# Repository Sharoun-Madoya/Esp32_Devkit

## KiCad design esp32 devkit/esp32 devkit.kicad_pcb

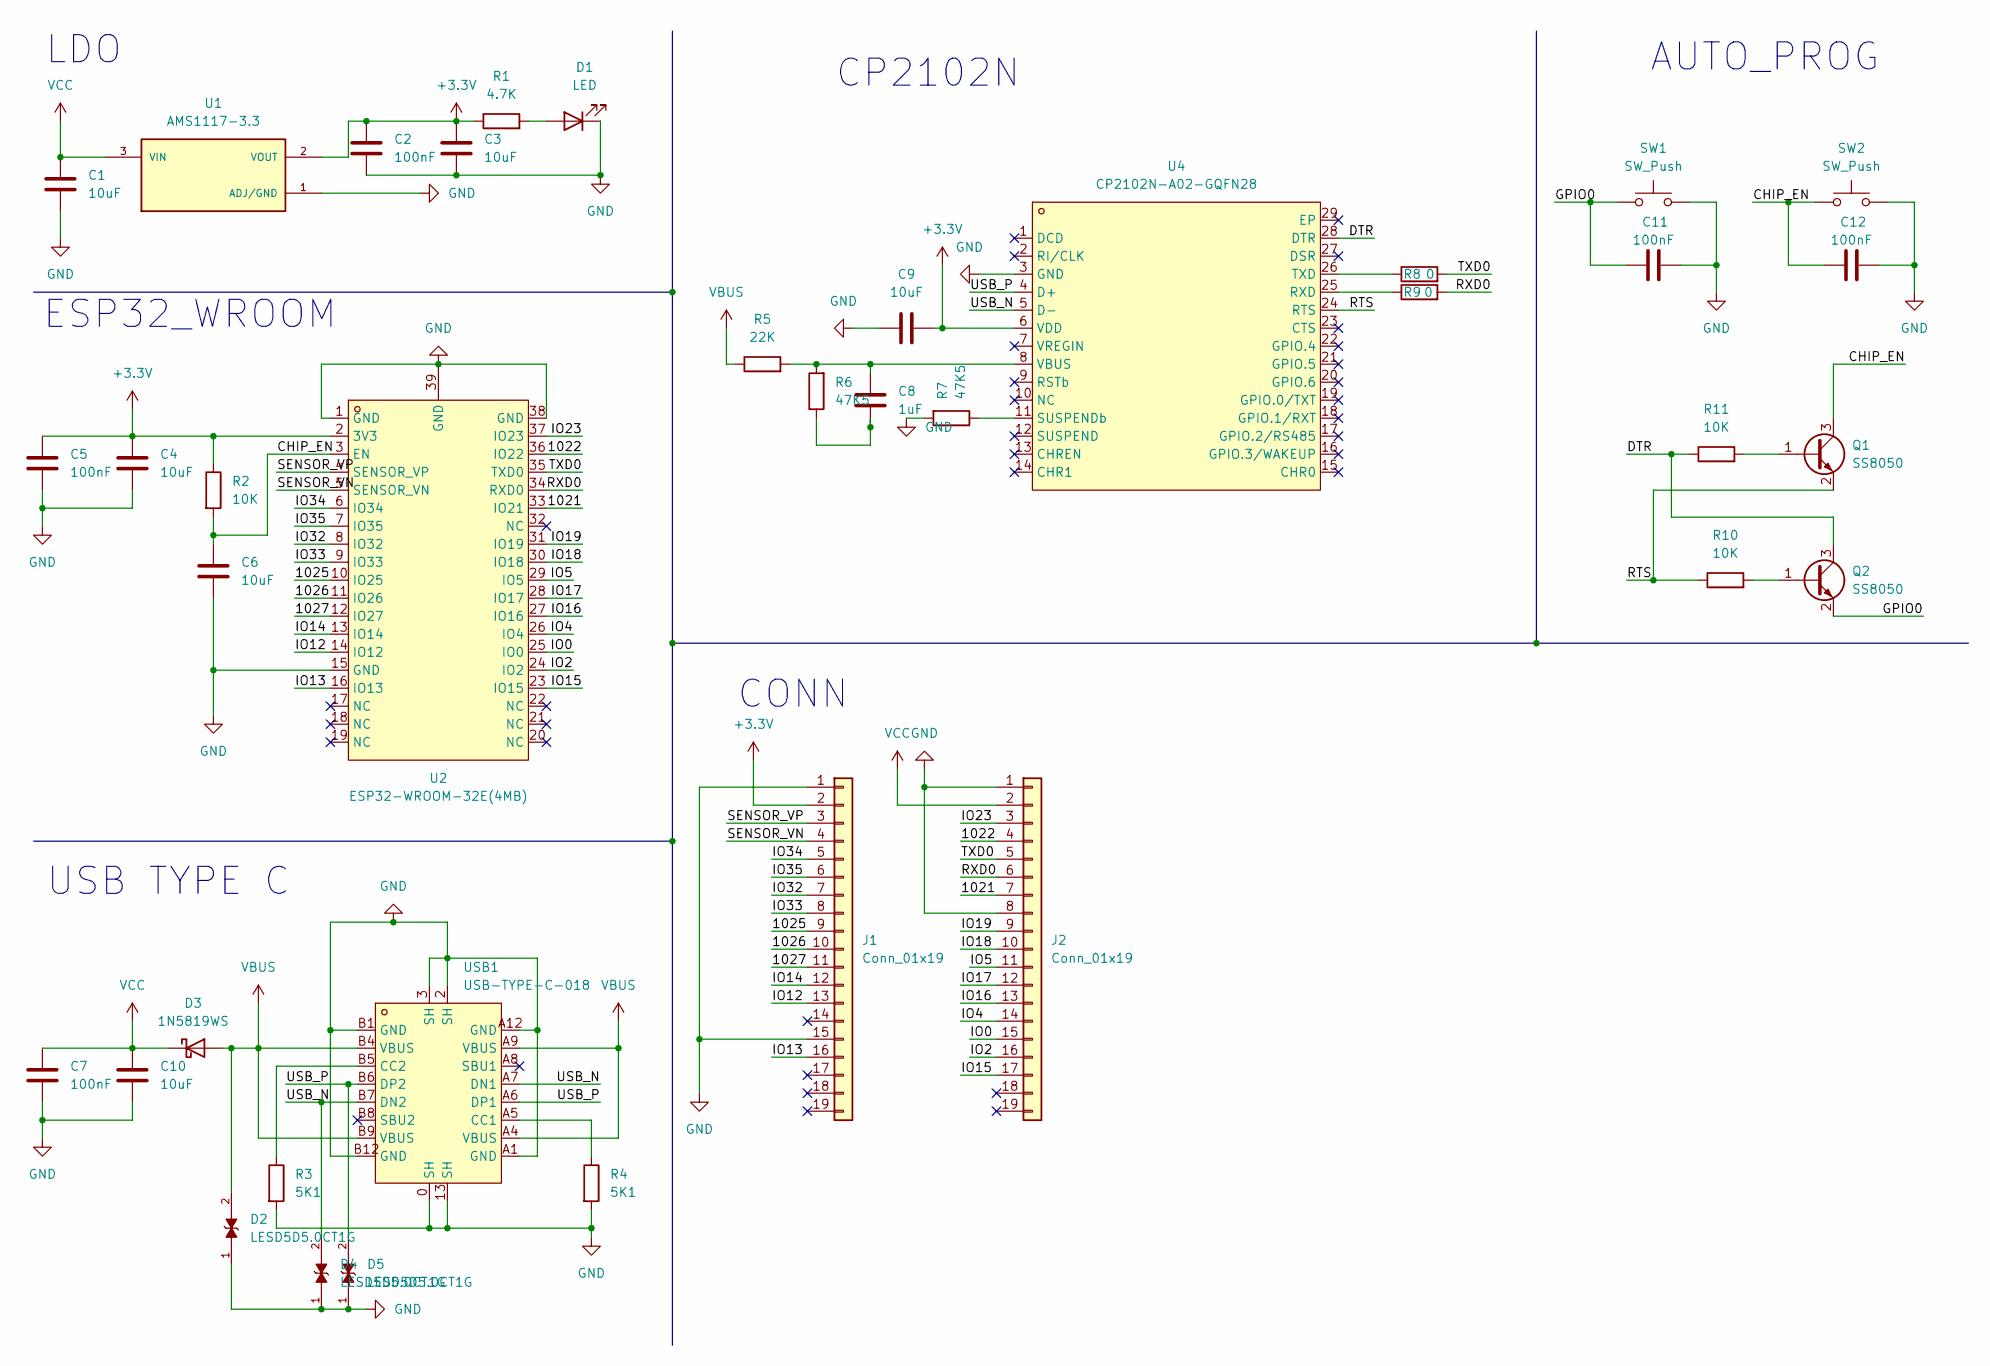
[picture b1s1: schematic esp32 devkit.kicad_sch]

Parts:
C1, C3, C4, C6, C9, C10: 10uF; C_0603_1608Metric
C2, C5, C7, C11, C12: 100nF; C_0402_1005Metric
C8: 1uF; C_0402_1005Metric
D1: LED; LED_0402_1005Metric
D2, D4, D5: LESD5D5.0CT1G; TVS_LESD5D5.0CT1G; PARTREV O
D3: 1N5819WS; D_SOD-323
J1, J2: Conn_01x19; PinHeader_1x19_P2.54mm_Vertical
Q1, Q2: SS8050; SOT-23
R1: 4.7K; R_0402_1005Metric
R2, R10, R11: 10K; R_0402_1005Metric
R3, R4: 5K1; R_0402_1005Metric
R5: 22K; R_0402_1005Metric
R6, R7: 47K5; R_0402_1005Metric
R8, R9: 0; R_0402_1005Metric
SW1, SW2: SW_Push; SW_SPST_TL3305A
U1: AMS1117-3.3; SOT-223-3_TabPin2; PARTREV NA; DigiKey_Part_Number 4518-AMS1117-3.3CT-ND
U2: ESP32-WROOM-32E(4MB); WIFI-SMD_ESP32-WROOM-32E; LCSC Part C701341
U4: CP2102N-A02-GQFN28; QFN-28_L5.0-W5.0-P0.50-TL-EP3.3; LCSC Part C1550553
USB1: USB-TYPE-C-018; USB-C_SMD-TYPE-C-31-M-12; LCSC Part C2927038

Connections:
+3.3V: C2.2, C3.1, C4.1, C5.2, C9.2, J1.2, R1.1, R2.1, U1.2 (VOUT), U2.2 (3V3), U4.6 (VDD)
/1021: J2.7, U2.33 (IO21)
/1022: J2.4, U2.36 (IO22)
/1025: J1.9, U2.10 (IO25)
/1026: J1.10, U2.11 (IO26)
/1027: J1.11, U2.12 (IO27)
/CHIP_EN: C6.1, C12.2, Q1.3 (C), R2.2, SW2.1, U2.3 (EN)
/DTR: Q2.3 (C), R11.1, U4.28 (DTR)
/GPIO0: C11.2, Q2.2 (E), SW1.1
/IO0: J2.15, U2.25 (IO0)
/IO2: J2.16, U2.24 (IO2)
/IO4: J2.14, U2.26 (IO4)
/IO5: J2.11, U2.29 (IO5)
/IO12: J1.13, U2.14 (IO12)
/IO13: J1.16, U2.16 (IO13)
/IO14: J1.12, U2.13 (IO14)
/IO15: J2.17, U2.23 (IO15)
/IO16: J2.13, U2.27 (IO16)
/IO17: J2.12, U2.28 (IO17)
/IO18: J2.10, U2.30 (IO18)
/IO19: J2.9, U2.31 (IO19)
/IO23: J2.3, U2.37 (IO23)
/IO32: J1.7, U2.8 (IO32)
/IO33: J1.8, U2.9 (IO33)
/IO34: J1.5, U2.6 (IO34)
/IO35: J1.6, U2.7 (IO35)
/RTS: Q1.2 (E), R10.1, U4.24 (RTS)
/RXD0: J2.6, R9.2, U2.34 (RXD0)
/SENSOR_VN: J1.4, U2.5 (SENSOR_VN)
/SENSOR_VP: J1.3, U2.4 (SENSOR_VP)
/TXD0: J2.5, R8.2, U2.35 (TXD0)
/USB_N: D4.2, U4.5 (D-), USB1.A7 (DN1), USB1.B7 (DN2)
/USB_P: D5.2, U4.4 (D+), USB1.A6 (DP1), USB1.B6 (DP2)
GND: C1.2, C2.1, C3.2, C4.2, C5.1, C6.2, C7.1, C9.1, C10.2, C11.1, C12.1, D1.1 (K), D2.1, D4.1, D5.1, J1.1, J1.15, J2.1, J2.8, R3.2, R4.2, R7.2, SW1.2, SW2.2, U1.1 (ADJ/GND), U2.1 (GND), U2.15 (GND), U2.38 (GND), U2.39 (GND), U4.3 (GND), USB1.0 (SH), USB1.2 (SH), USB1.3 (SH), USB1.13 (SH), USB1.A1 (GND), USB1.A12 (GND), USB1.B1 (GND), USB1.B12 (GND)
unnamed: C8.2, R6.1
unnamed: D1.2 (A), R1.2
unnamed: Q1.1 (B), R11.2
unnamed: Q2.1 (B), R10.2
unnamed: R9.1, U4.25 (RXD)
unnamed: R7.1, U4.11 (SUSPENDb)
unnamed: R8.1, U4.26 (TXD)
unnamed: C8.1, R5.2, R6.2, U4.8 (VBUS)
unnamed: R4.1, USB1.A5 (CC1)
unnamed: R3.1, USB1.B5 (CC2)
VBUS: D2.2, D3.2 (A), R5.1, USB1.A4 (VBUS), USB1.A9 (VBUS), USB1.B4 (VBUS), USB1.B9 (VBUS)
VCC: C1.1, C7.2, C10.1, D3.1 (K), J2.2, U1.3 (VIN)

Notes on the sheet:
ESP32_WROOM
CP2102N
USB TYPE C
AUTO_PROG
CONN
LDO

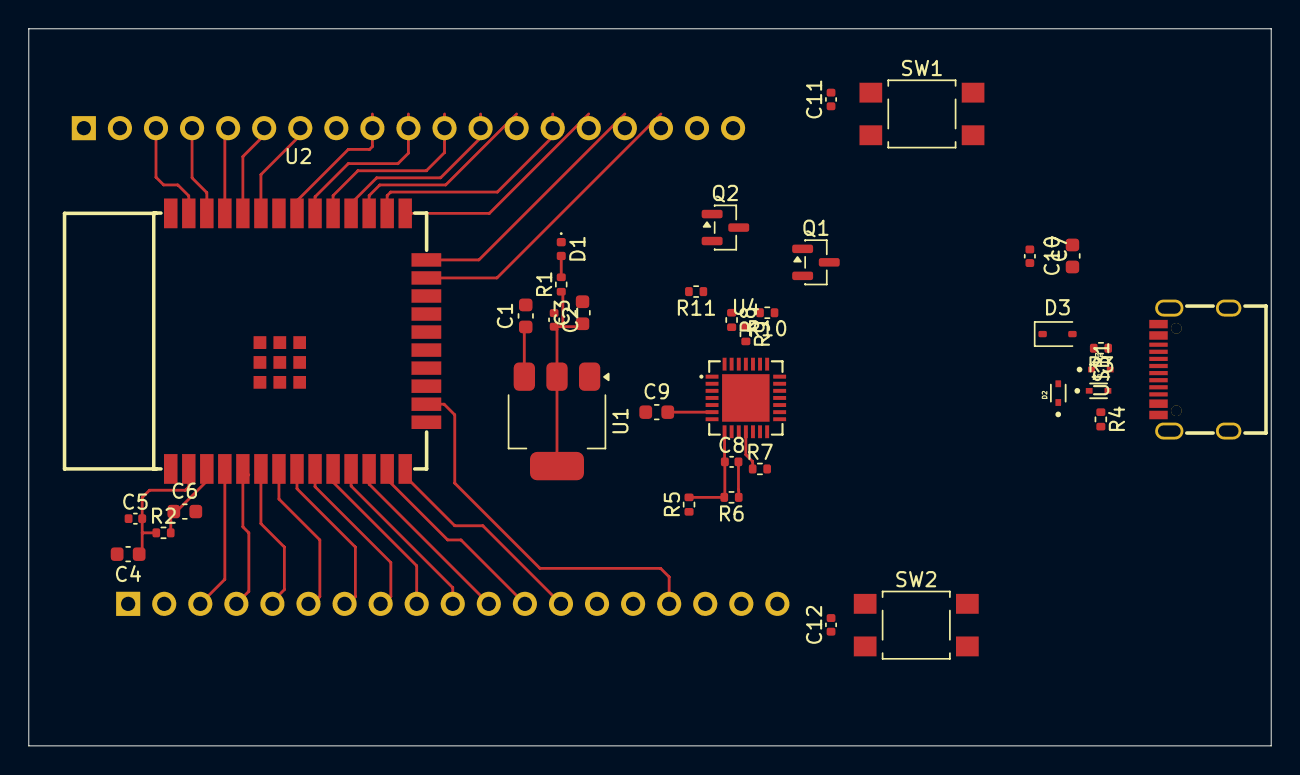
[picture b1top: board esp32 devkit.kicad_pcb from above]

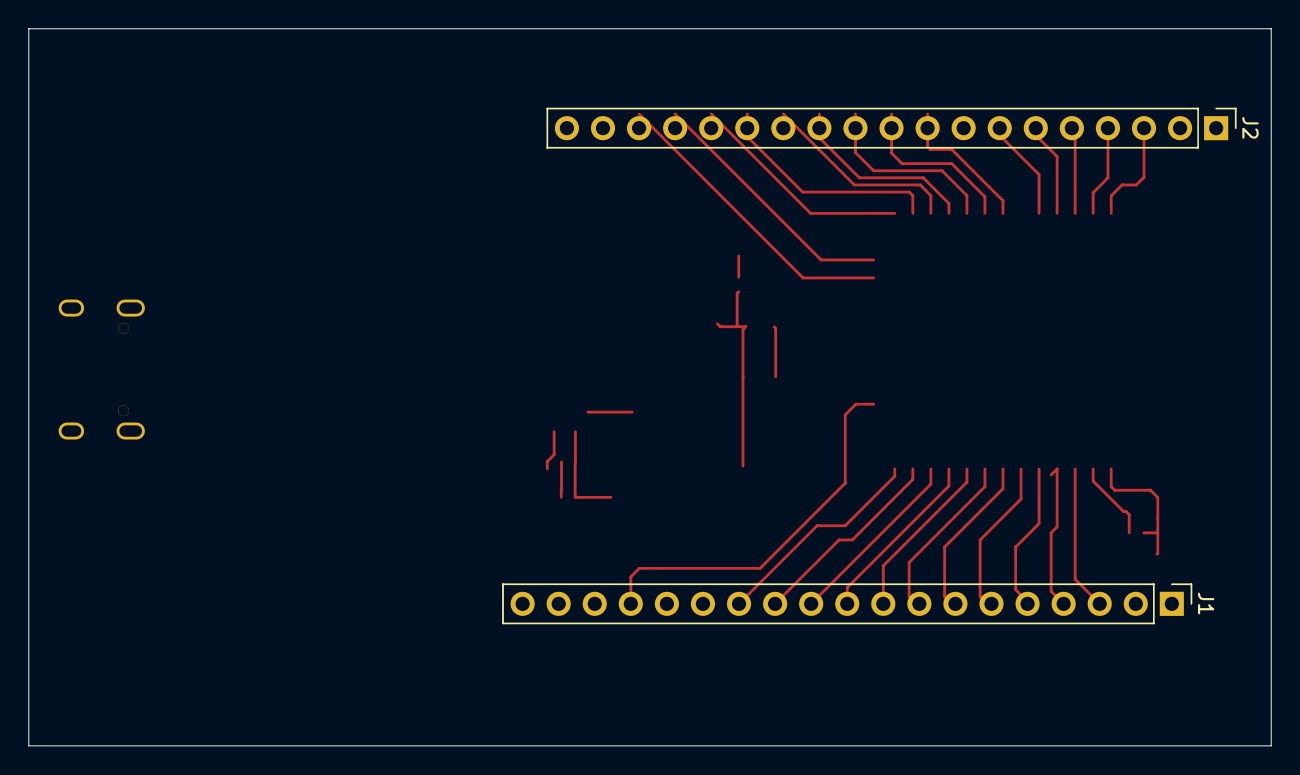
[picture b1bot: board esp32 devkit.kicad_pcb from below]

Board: 2 copper layers, 87.5 x 50.5 mm, 38 parts (2 on the bottom side), 46 nets.

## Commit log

2025-11-07 :: started with basic filter componets for esp
2025-11-11 :zap: changed esp32 and added ams
2025-11-16 :construction: ADDED USB TYP C N UART
2025-11-17 :green_heart: completing the connectors
2025-11-23 :rocket: completed electrical checker rules
2025-11-30 :bug:Fixed errors of footprint,, started on Editor
2025-12-02 :bug:changed CP2102 footprint and schematic
2025-12-02 :lipstick::bug:changed LESD5 FOOTPRINT
2025-12-02 :memo:Connected LDO AND ESP in editor
2025-12-03 :tada:Completed grounding in filled zones and wiring at the editor
